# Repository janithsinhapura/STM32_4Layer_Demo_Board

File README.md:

Contains the project files of the design of a 4 layer STM32F103c8t6 Demo Board

+ SPI
+ I2C
+ UART
+ USB

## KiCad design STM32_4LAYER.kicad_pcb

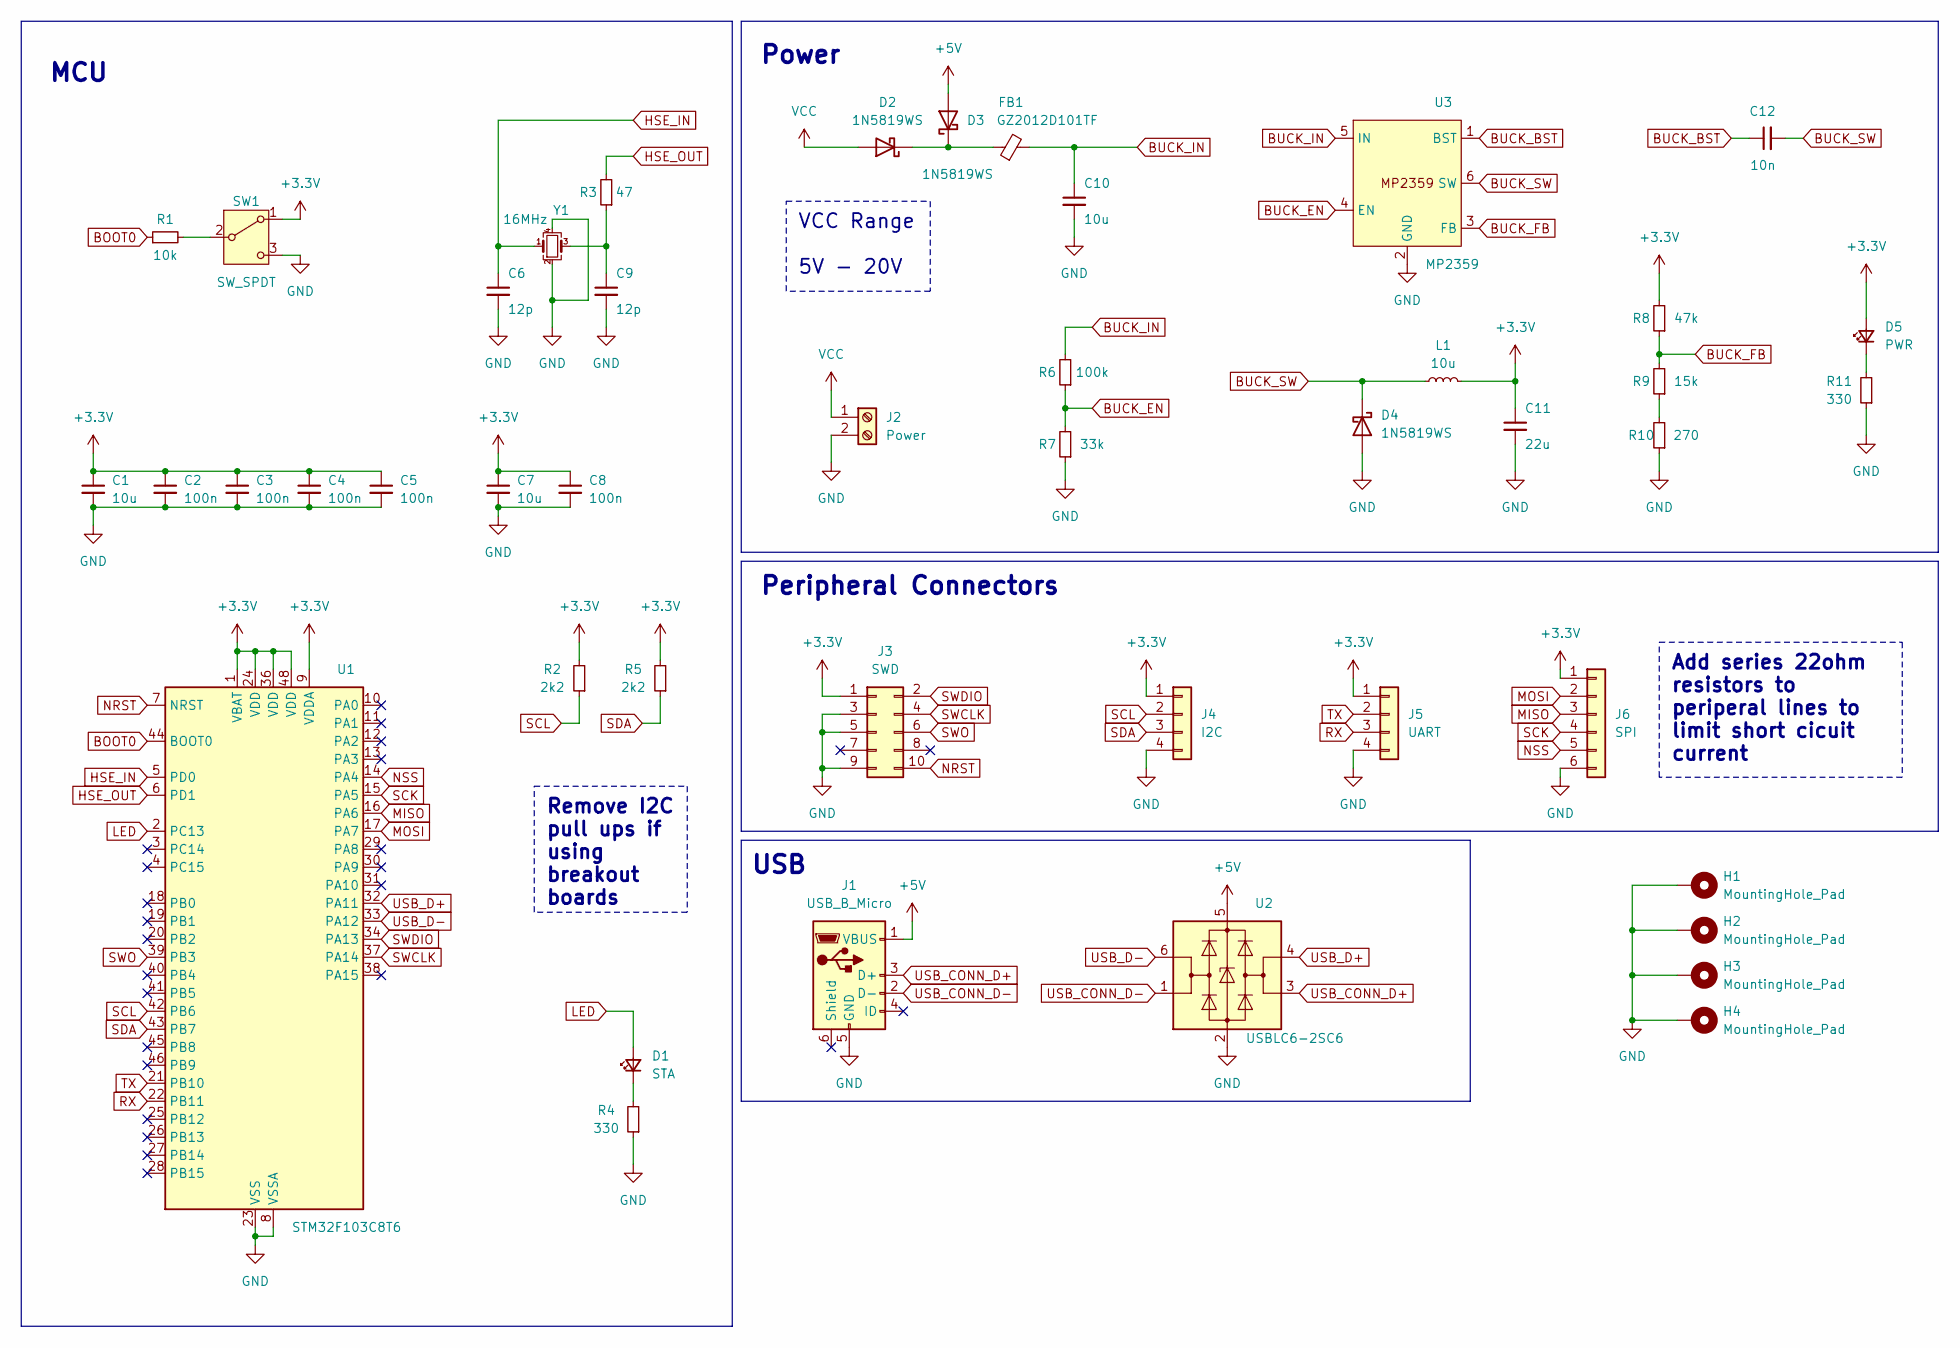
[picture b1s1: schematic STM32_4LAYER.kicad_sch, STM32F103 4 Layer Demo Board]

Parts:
C1, C7: 10u; C_0603_1608Metric
C2, C3, C4, C5, C8: 100n; C_0402_1005Metric
C6, C9: 12p; C_0402_1005Metric
C10: 10u; C_1206_3216Metric
C11: 22u; C_1206_3216Metric
C12: 10n; C_0402_1005Metric
D1: STA; LED_0603_1608Metric
D2, D3, D4: 1N5819WS; D_SOD-323
D5: PWR; LED_0603_1608Metric
FB1: GZ2012D101TF; L_0805_2012Metric
H1, H2, H3, H4: MountingHole_Pad; MountingHole_4.3mm_M4_Pad_Via
J1: USB_B_Micro; USB_Micro-B_Molex_47346-0001
J2: Power; TerminalBlock_Phoenix_PT-1,5-2-3.5-H_1x02_P3.50mm_Horizontal
J3: SWD; PinHeader_2x05_P1.27mm_Vertical_SMD
J4: I2C; Molex_PicoBlade_53048-0410_1x04_P1.25mm_Horizontal
J5: UART; Molex_PicoBlade_53048-0410_1x04_P1.25mm_Horizontal
J6: SPI; Molex_PicoBlade_53048-0610_1x06_P1.25mm_Horizontal
L1: 10u; L_Sunlord_MWSA0518S
R1: 10k; R_0402_1005Metric
R2, R5: 2k2; R_0402_1005Metric
R3: 47; R_0402_1005Metric
R4, R11: 330; R_0603_1608Metric
R6: 100k; R_0603_1608Metric
R7: 33k; R_0603_1608Metric
R8: 47k; R_0603_1608Metric
R9: 15k; R_0603_1608Metric
R10: 270; R_0603_1608Metric
SW1: SW_SPDT; SW_SPDT_PCM12
U1: STM32F103C8T6; LQFP-48_7x7mm_P0.5mm
U2: USBLC6-2SC6; SOT-23-6
U3: MP2359; TSOT-23-6
Y1: 16MHz; Crystal_SMD_3225-4Pin_3.2x2.5mm

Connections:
+3.3V: C1.1, C2.1, C3.1, C4.1, C5.1, C7.1, C8.1, C11.1, D5.2 (A), J3.1, J4.1, J5.1, J6.1, L1.2, R2.2, R5.2, R8.2, SW1.1 (A), U1.1 (VBAT), U1.9 (VDDA), U1.24 (VDD), U1.36 (VDD), U1.48 (VDD)
+5V: D3.2 (A), J1.1 (VBUS), U2.5 (VBUS)
BOOT0: R1.1, U1.44 (BOOT0)
BUCK_BST: C12.1, U3.1 (BST)
BUCK_EN: R6.1, R7.2, U3.4 (EN)
BUCK_FB: R8.1, R9.2, U3.3 (FB)
BUCK_IN: C10.1, FB1.2, R6.2, U3.5 (IN)
BUCK_SW: C12.2, D4.1 (K), L1.1, U3.6 (SW)
GND: C1.2, C2.2, C3.2, C4.2, C5.2, C6.2, C7.2, C8.2, C9.2, C10.2, C11.2, D4.2 (A), H1.1, H2.1, H3.1, H4.1, J1.5 (GND), J2.2, J3.3, J3.5, J3.9, J4.4, J5.4, J6.6, R4.1, R7.1, R10.1, R11.1, SW1.3 (C), U1.8 (VSSA), U1.23 (VSS), U1.35 (VSS), U1.47 (VSS), U2.2 (GND), U3.2 (GND), Y1.2, Y1.4
HSE_IN: C6.1, U1.5 (PD0), Y1.1
HSE_OUT: R3.2, U1.6 (PD1)
LED: D1.2 (A), U1.2 (PC13)
MISO: J6.3, U1.16 (PA6)
MOSI: J6.2, U1.17 (PA7)
NRST: J3.10, U1.7 (NRST)
NSS: J6.5, U1.14 (PA4)
unnamed: C9.1, R3.1, Y1.3
unnamed: D1.1 (K), R4.2
unnamed: D2.1 (K), D3.1 (K), FB1.1
unnamed: D5.1 (K), R11.2
unnamed: R9.1, R10.2
unnamed: R1.2, SW1.2 (B)
RX: J5.3, U1.22 (PB11)
SCK: J6.4, U1.15 (PA5)
SCL: J4.2, R2.1, U1.42 (PB6)
SDA: J4.3, R5.1, U1.43 (PB7)
SWCLK: J3.4, U1.37 (PA14)
SWDIO: J3.2, U1.34 (PA13)
SWO: J3.6, U1.39 (PB3)
TX: J5.2, U1.21 (PB10)
USB_CONN_D+: J1.3 (D+), U2.3 (I/O2)
USB_CONN_D-: J1.2 (D-), U2.1 (I/O1)
USB_D+: U1.32 (PA11), U2.4 (I/O2)
USB_D-: U1.33 (PA12), U2.6 (I/O1)
VCC: D2.2 (A), J2.1

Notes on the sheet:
Remove I2C pull ups if using breakout boards
VCC Range 5V - 20V
Add series 22ohm resistors to periperal lines to limit short cicuit current
Peripheral Connectors
Power
MCU
USB

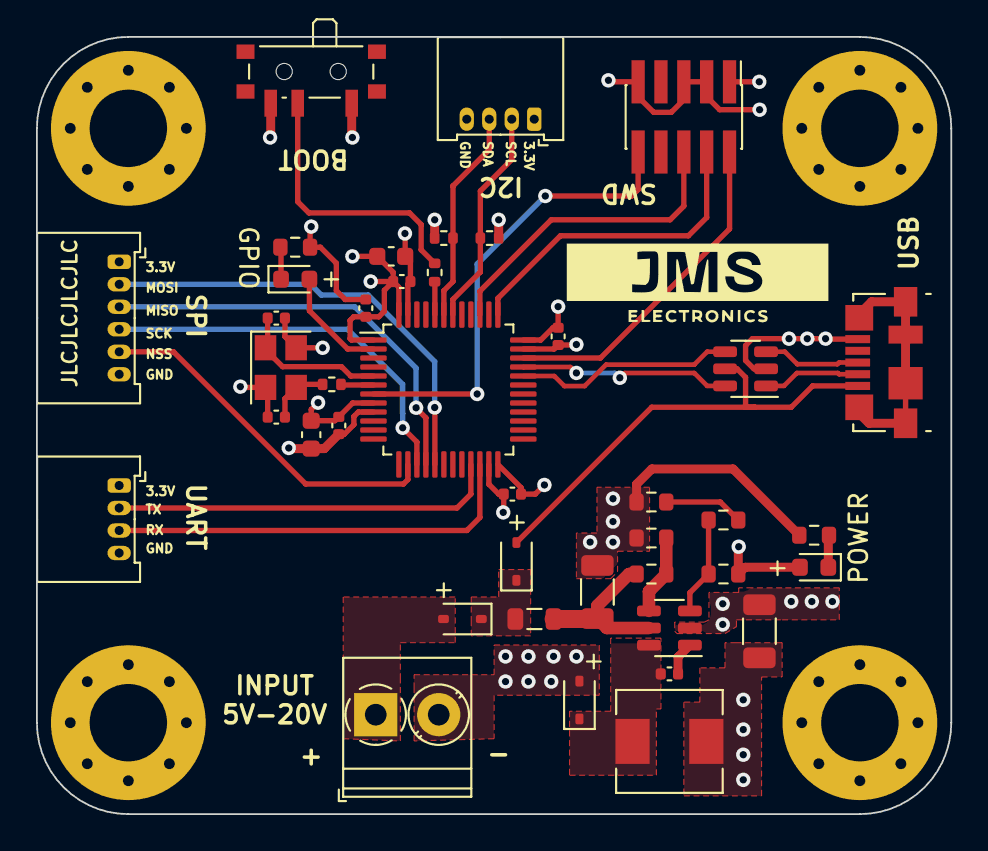
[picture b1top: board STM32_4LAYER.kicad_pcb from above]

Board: 4 copper layers, 50.8 x 43.2 mm, 45 parts (0 on the bottom side), 35 nets.

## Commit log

2024-03-14 Added the project files
